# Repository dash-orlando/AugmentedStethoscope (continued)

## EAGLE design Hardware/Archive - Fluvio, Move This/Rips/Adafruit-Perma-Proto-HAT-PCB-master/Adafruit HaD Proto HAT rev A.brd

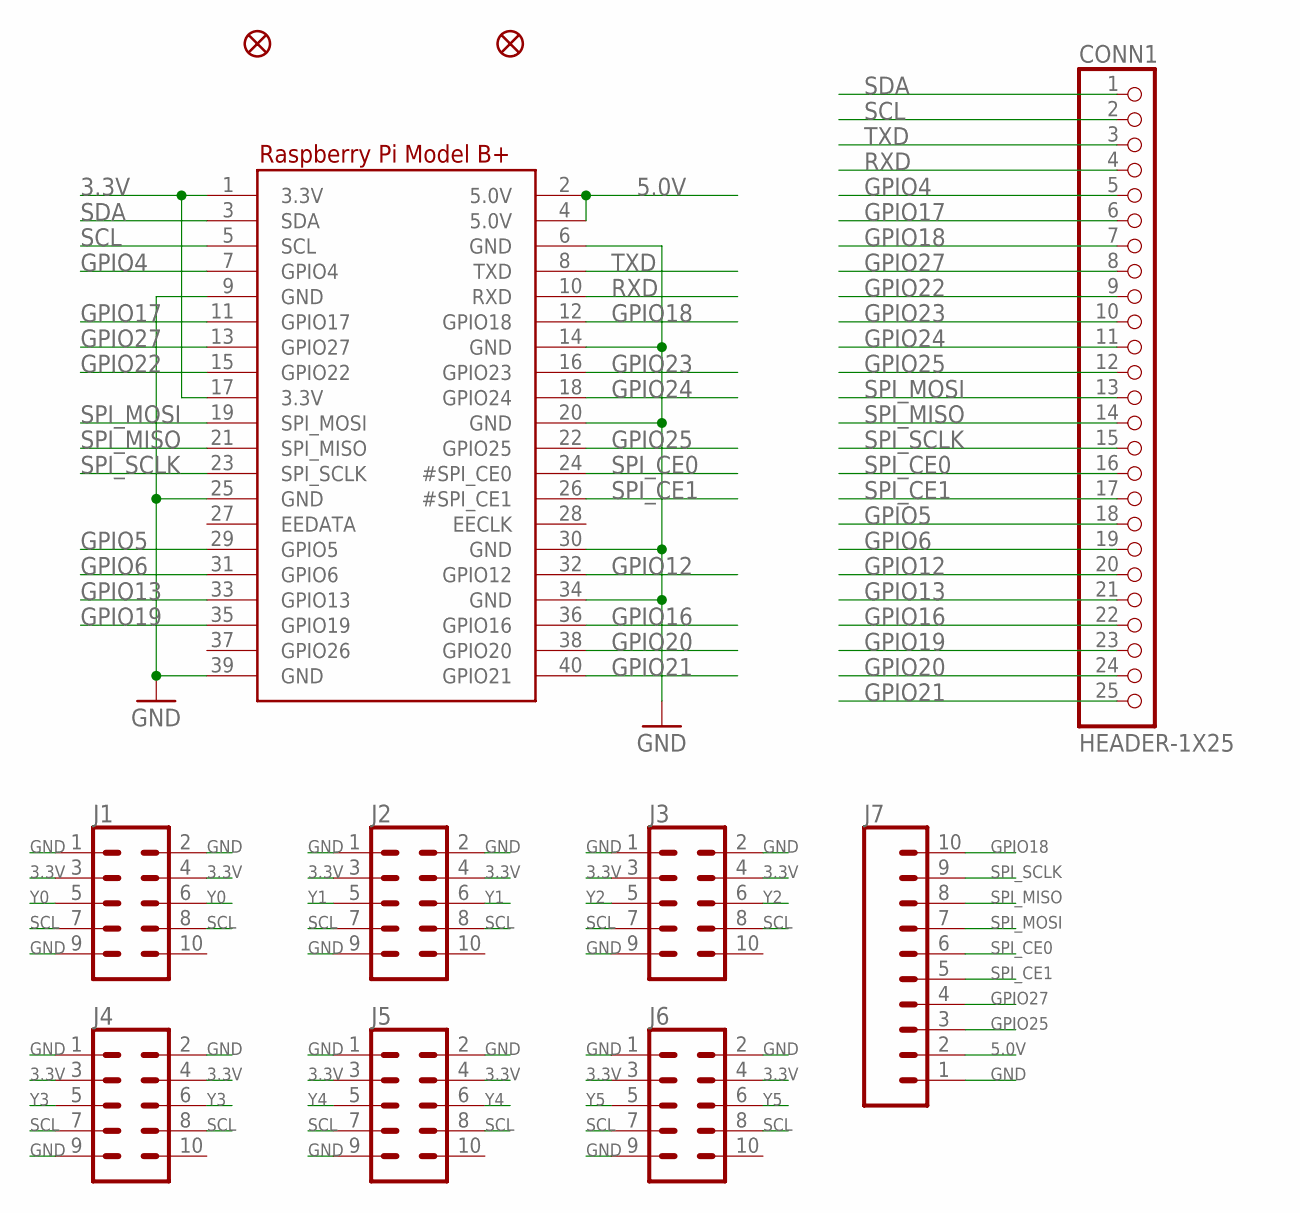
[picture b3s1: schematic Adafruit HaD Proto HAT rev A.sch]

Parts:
CONN1: HEADER-1X25; 1X25_ROUND_70MIL
FID2, FID3: FIDUCIAL""; FIDUCIAL_1MM
J1, J2, J3, J4, J5, J6: CONN_05X2SHD; 2X5-SHROUDED
J7: CONN_10LOCK; 1X10_LOCK
RPI1: RASPBERRYPI_BPLUS_HATNOSLOTS; PI_HAT_NOSLOTS

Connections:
3.3V: J1.3, J1.4, J2.3, J2.4, J3.3, J3.4, J4.3, J4.4, J5.3, J5.4, J6.3, J6.4, RPI1.1 (3.3V), RPI1.17 (3.3V)
5.0V: J7.2, RPI1.2 (5.0V), RPI1.4 (5.0V)
GND: J1.1, J1.2, J1.9, J2.1, J2.2, J2.9, J3.1, J3.2, J3.9, J4.1, J4.2, J4.9, J5.1, J5.2, J5.9, J6.1, J6.2, J6.9, J7.1, RPI1.6 (GND), RPI1.9 (GND), RPI1.14 (GND), RPI1.20 (GND), RPI1.25 (GND), RPI1.30 (GND), RPI1.34 (GND), RPI1.39 (GND)
GPIO4: CONN1.5, RPI1.7 (GPIO4)
GPIO5: CONN1.18, RPI1.29 (GPIO5)
GPIO6: CONN1.19, RPI1.31 (GPIO6)
GPIO12: CONN1.20, RPI1.32 (GPIO12)
GPIO13: CONN1.21, RPI1.33 (GPIO13)
GPIO16: CONN1.22, RPI1.36 (GPIO16)
GPIO17: CONN1.6, RPI1.11 (GPIO17)
GPIO18: CONN1.7, J7.10, RPI1.12 (GPIO18)
GPIO19: CONN1.23, RPI1.35 (GPIO19)
GPIO20: CONN1.24, RPI1.38 (GPIO20)
GPIO21: CONN1.25, RPI1.40 (GPIO21)
GPIO22: CONN1.9, RPI1.15 (GPIO22)
GPIO23: CONN1.10, RPI1.16 (GPIO23)
GPIO24: CONN1.11, RPI1.18 (GPIO24)
GPIO25: CONN1.12, J7.3, RPI1.22 (GPIO25)
GPIO27: CONN1.8, J7.4, RPI1.13 (GPIO27)
RXD: CONN1.4, RPI1.10 (RXD)
SCL: CONN1.2, J1.7, J1.8, J2.7, J2.8, J3.7, J3.8, J4.7, J4.8, J5.7, J5.8, J6.7, J6.8, RPI1.5 (SCL)
SDA: CONN1.1, RPI1.3 (SDA)
SPI_CE0: CONN1.16, J7.6, RPI1.24 (#SPI_CE0)
SPI_CE1: CONN1.17, J7.5, RPI1.26 (#SPI_CE1)
SPI_MISO: CONN1.14, J7.8, RPI1.21 (SPI_MISO)
SPI_MOSI: CONN1.13, J7.7, RPI1.19 (SPI_MOSI)
SPI_SCLK: CONN1.15, J7.9, RPI1.23 (SPI_SCLK)
TXD: CONN1.3, RPI1.8 (TXD)
Y0: J1.5, J1.6
Y1: J2.5, J2.6
Y2: J3.5, J3.6
Y3: J4.5, J4.6
Y4: J5.5, J5.6
Y5: J6.5, J6.6

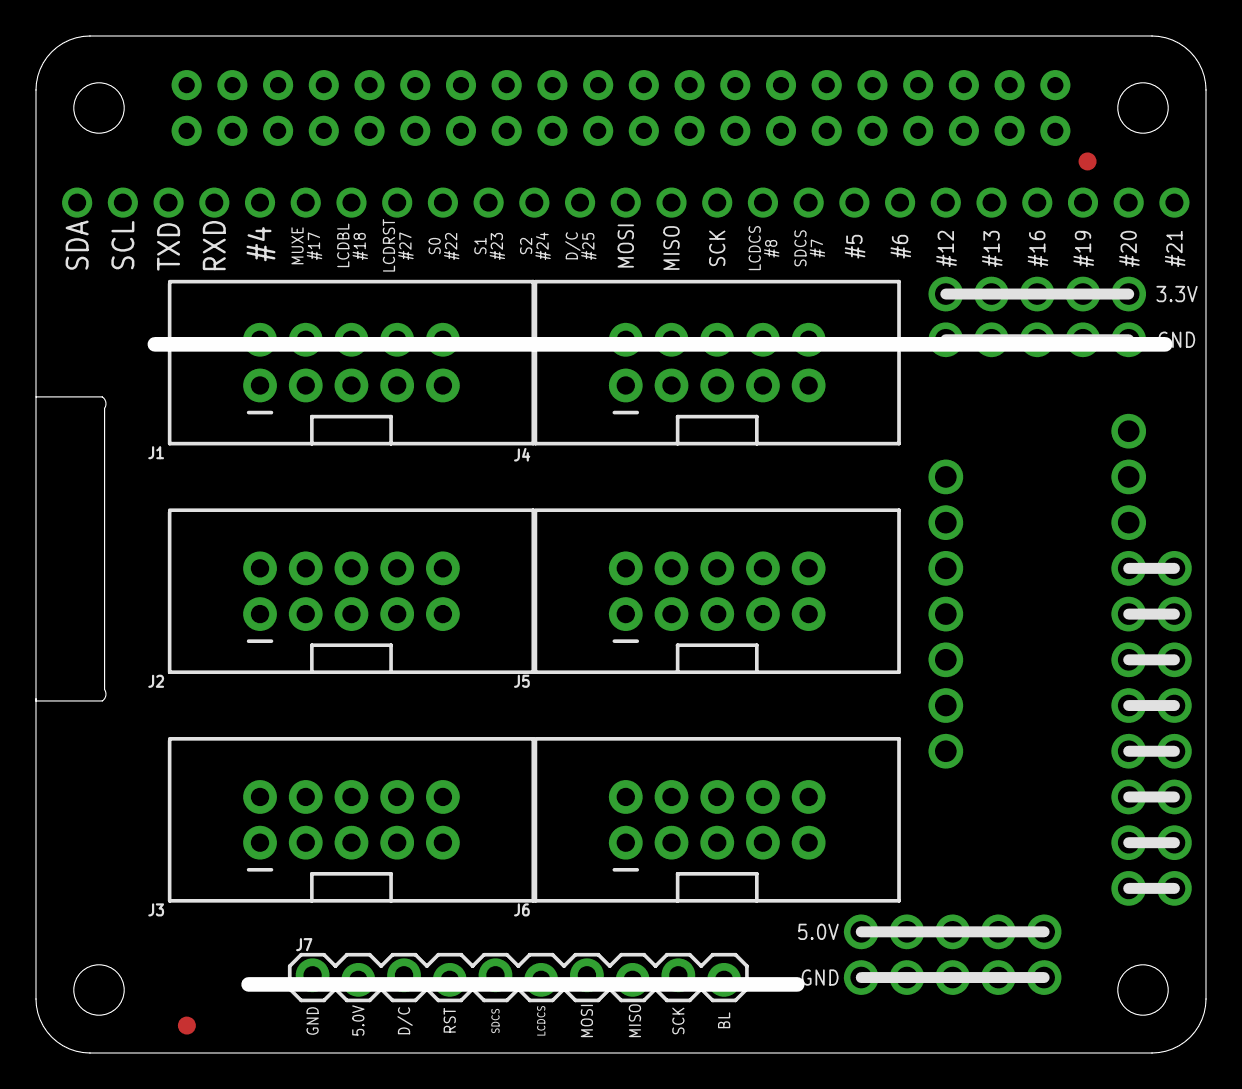
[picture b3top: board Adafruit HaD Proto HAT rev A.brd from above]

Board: 2 copper layers, 65.0 x 56.5 mm, 11 parts (0 on the bottom side), 34 nets.

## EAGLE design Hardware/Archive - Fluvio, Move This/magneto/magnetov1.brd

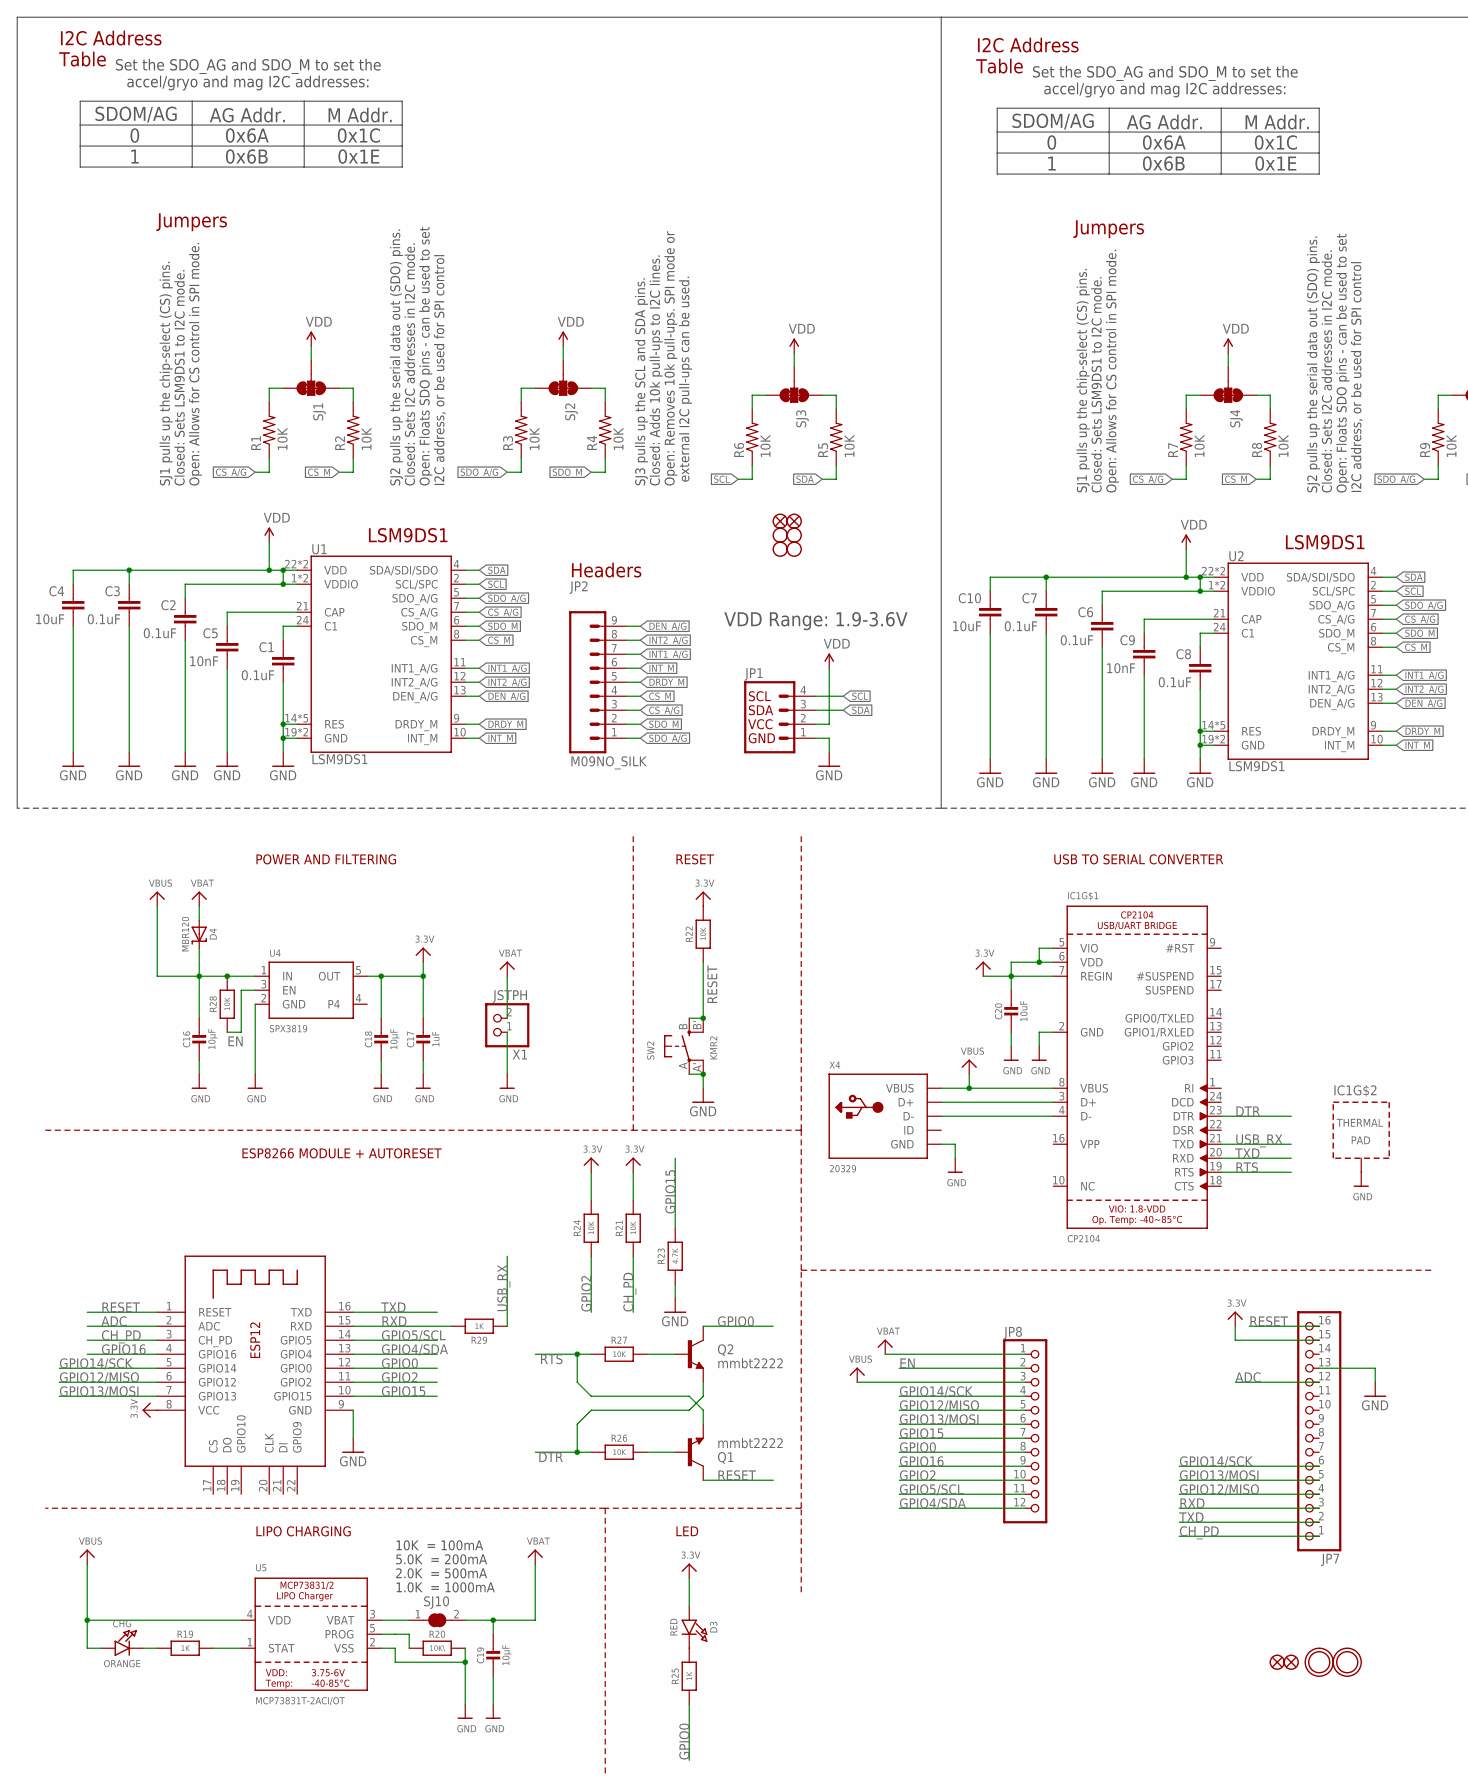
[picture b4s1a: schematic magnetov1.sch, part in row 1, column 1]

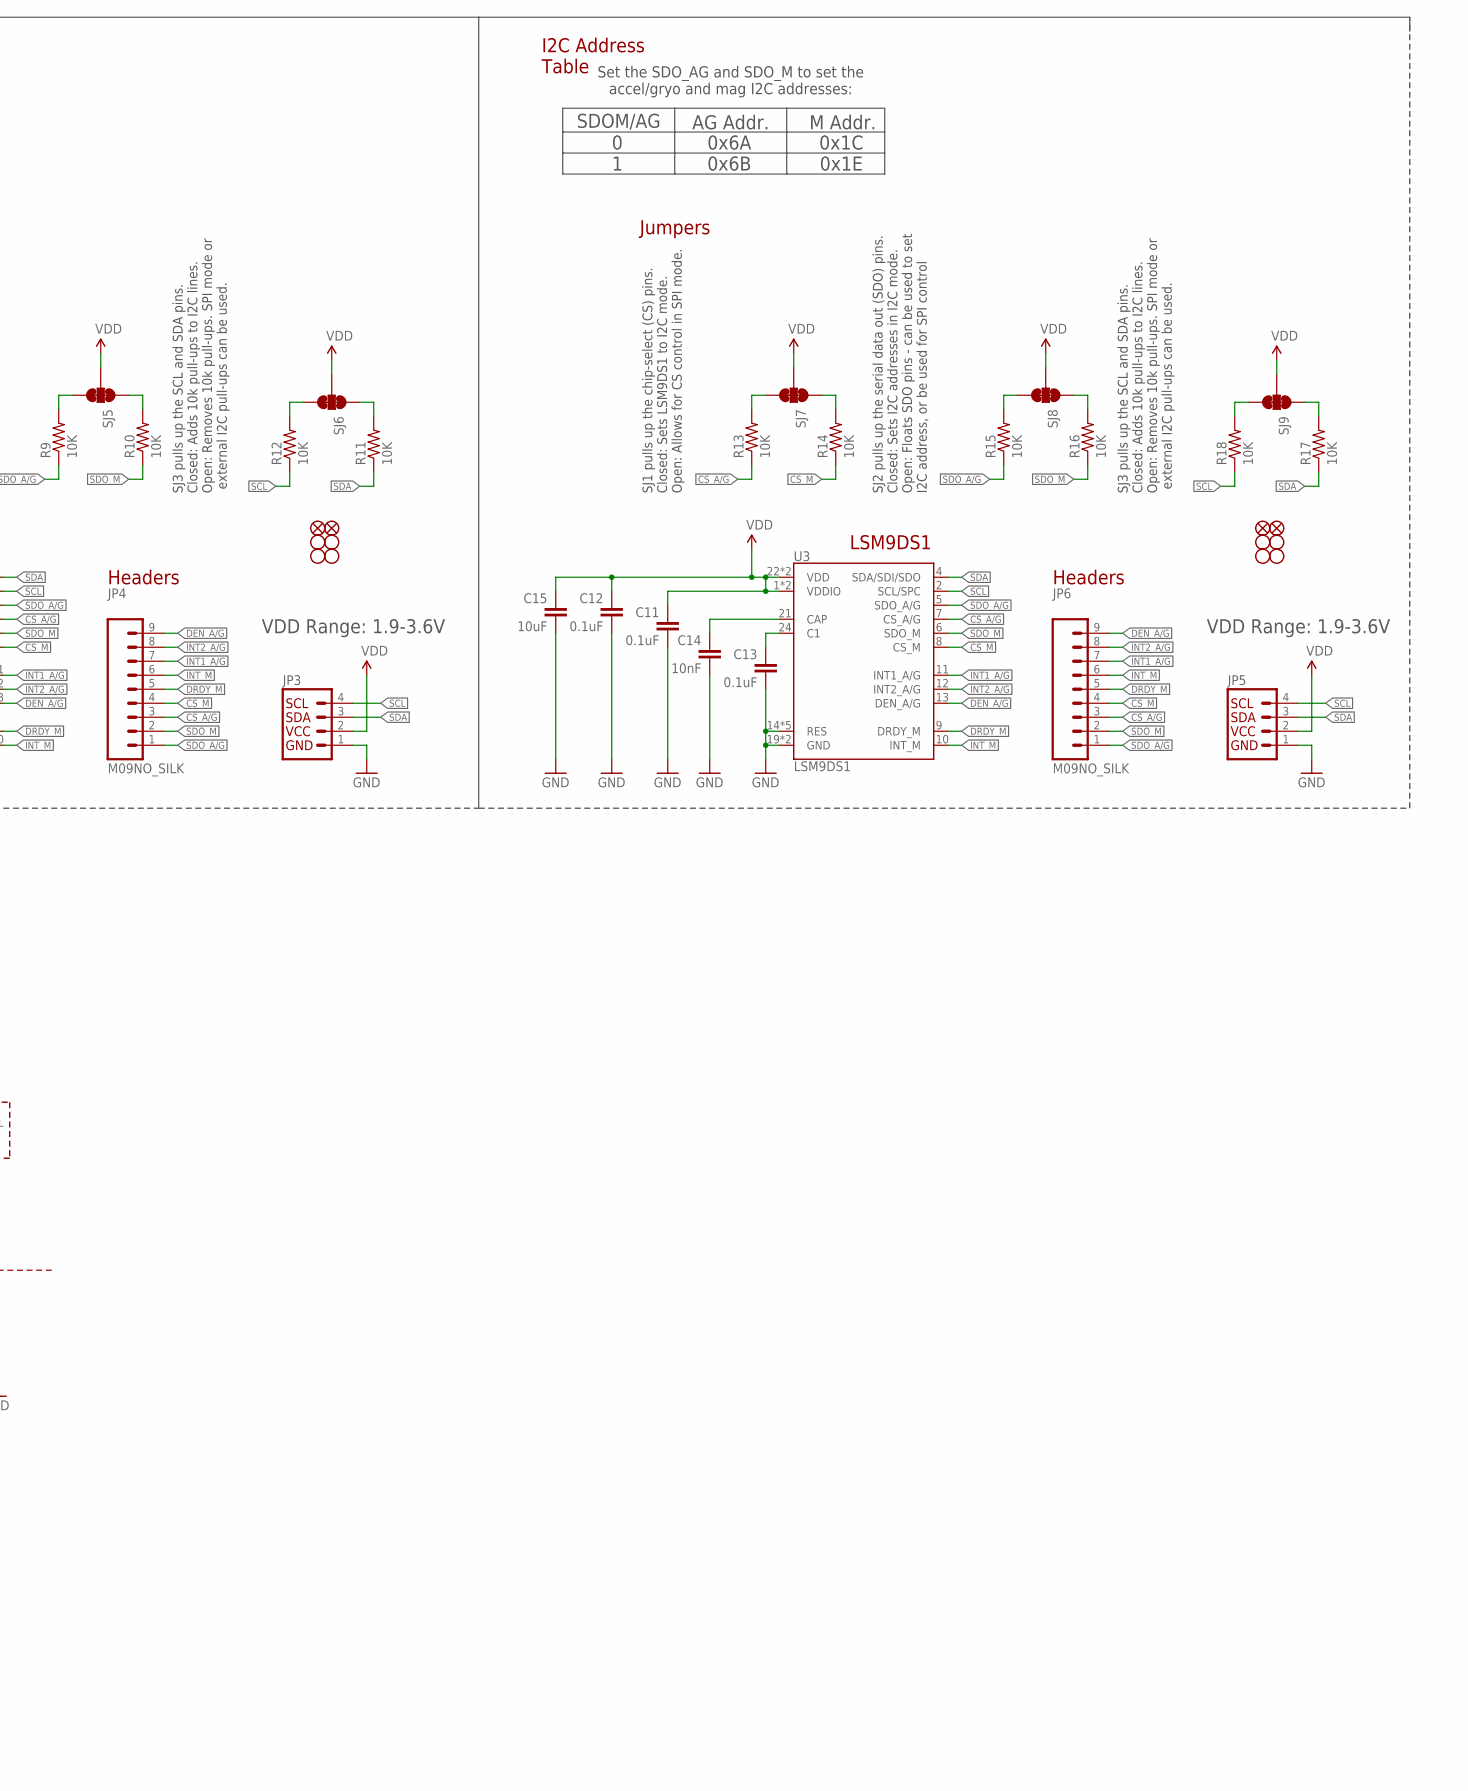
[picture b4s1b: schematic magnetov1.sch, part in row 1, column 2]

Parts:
C1, C2, C3, C6, C7, C8, C11, C12, C13: 0.1uF; 0603-CAP
C4, C10, C15: 10uF; 0603-CAP
C5, C9, C14: 10nF; 0603-CAP
C16, C18, C19: 10µF; 0805-NO
C17: 1uF; 0603-NO
C20: 10uF; 0805-NO
CHG: ORANGE; CHIPLED_0805_NOOUTLINE
D3: RED; CHIPLED_0805_NOOUTLINE
D4: MBR120; SOD-123
FID1, FID2, FID3, FID4, FID5, FID6: FIDUCIAL1X2; FIDUCIAL-1X2
IC1: CP2104; QFN24_4MM_SMSC
JP1, JP3, JP5: I2C_STANDARD_NO_SILK; 1X04_NO_SILK
JP2, JP4, JP6: M09NO_SILK; 1X09_NO_SILK
JP7: HEADER-1X16ROUND; 1X16_ROUND
JP8: HEADER-1X12; 1X12_ROUND
Q1, Q2: mmbt2222; SOT23-3
R1, R2, R3, R4, R5, R6, R7, R8, R9, R10, R11, R12, R13, R14, R15, R16, R17, R18: 10K; 0603-RES
R19, R25: 1K; 0603-NO
R20: 10K\; 0603-NO
R21, R22, R24, R26, R28: 10K; 0603-NO
R23: 4.7K; 0603-NO
R27: 10K; _0603MP
R29: 1K; _0603MP
SJ1, SJ2, SJ3, SJ4, SJ5, SJ6, SJ7, SJ8, SJ9: JUMPER-PAD-3-NC_BY_TRACE; PAD-JUMPER-3-3OF3_NC_BY_TRACE_YES_SILK_FULL_BOX
SJ10: SOLDERJUMPER_CLOSED; SOLDERJUMPER_CLOSEDWIRE
STANDOFF1, STANDOFF2, STANDOFF3, STANDOFF4, STANDOFF5, STANDOFF6, STANDOFF7, STANDOFF8, STANDOFF9, STANDOFF10, STANDOFF11, STANDOFF12: STAND-OFF
SW2: KMR2; BTN_KMR2_4.6X2.8
U1, U2, U3: LSM9DS1; LGA24-8X4
U4: SPX3819; SOT23-5
U5: MCP73831T-2ACI/OT; SOT23-5
U$31, U$32: MOUNTINGHOLE2.5; MOUNTINGHOLE_2.5_PLATED
U$34, U$35: FIDUCIAL""; FIDUCIAL_1MM
X1: JSTPH; JSTPH2
X2: ESP-12; ESP-12E
X4: 20329; 4UCONN_20329_V2

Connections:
3.3V: C17.1, C18.1, C20.1, D3.A, IC1.5 (VIO), IC1.6 (VDD), IC1.7 (REGIN), JP7.15, R21.2, R22.2, R24.2, U4.5 (OUT), X2.8 (VCC)
ADC: JP7.12, X2.2 (ADC)
C1: C1.1, U1.24 (C1)
C2: C8.1, U2.24 (C1)
C3: C13.1, U3.24 (C1)
CAP: C5.1, U1.21 (CAP)
CAP1: C9.1, U2.21 (CAP)
CAP2: C14.1, U3.21 (CAP)
CH_PD: JP7.1, R21.1, X2.3 (CH_PD)
CS_A/G: JP2.3, JP4.3, JP6.3, R1.1, R7.1, R13.1, U1.7 (CS_A/G), U2.7 (CS_A/G), U3.7 (CS_A/G)
CS_A/G_PU: R1.2, SJ1.3
CS_A/G_PU1: R7.2, SJ4.3
CS_A/G_PU2: R13.2, SJ7.3
CS_M: JP2.4, JP4.4, JP6.4, R2.1, R8.1, R14.1, U1.8 (CS_M), U2.8 (CS_M), U3.8 (CS_M)
CS_M_PU: R2.2, SJ1.1
CS_M_PU1: R8.2, SJ4.1
CS_M_PU2: R14.2, SJ7.1
DEN_A/G: JP2.9, JP4.9, JP6.9, U1.13 (DEN_A/G), U2.13 (DEN_A/G), U3.13 (DEN_A/G)
DRDY_M: JP2.5, JP4.5, JP6.5, U1.9 (DRDY_M), U2.9 (DRDY_M), U3.9 (DRDY_M)
DTR: IC1.23 (DTR), Q2.2 (E), R26.1
EN: JP8.2, R28.1, U4.3 (EN)
GND: C1.2, C2.2, C3.2, C4.2, C5.2, C6.2, C7.2, C8.2, C9.2, C10.2, C11.2, C12.2, C13.2, C14.2, C15.2, C16.2, C17.2, C18.2, C19.2, C20.2, IC1.2 (GND), IC1.THERM (TP), JP1.1, JP3.1, JP5.1, JP7.13, R20.2, R23.1, SW2.A, SW2.A' (P1), U1.14 (RES), U1.15 (RES), U1.16 (RES), U1.17 (RES), U1.18 (RES), U1.19 (GND), U1.20 (GND), U2.14 (RES), U2.15 (RES), U2.16 (RES), U2.17 (RES), U2.18 (RES), U2.19 (GND), U2.20 (GND), U3.14 (RES), U3.15 (RES), U3.16 (RES), U3.17 (RES), U3.18 (RES), U3.19 (GND), U3.20 (GND), U4.2 (GND), U5.2 (VSS), X1.1, X2.9 (GND), X4.BASE@1 (GND), X4.BASE@2 (GND), X4.GND, X4.SPRT@1 (GND), X4.SPRT@2 (GND), X4.SPRT@3 (GND), X4.SPRT@4 (GND)
GPIO0: JP8.8, Q2.3 (C), R25.1, X2.12 (GPIO0)
GPIO2: JP8.10, R24.1, X2.11 (GPIO2)
GPIO4/SDA: JP8.12, X2.13 (GPIO4)
GPIO5/SCL: JP8.11, X2.14 (GPIO5)
GPIO12/MISO: JP7.4, JP8.5, X2.6 (GPIO12)
GPIO13/MOSI: JP7.5, JP8.6, X2.7 (GPIO13)
GPIO14/SCK: JP7.6, JP8.4, X2.5 (GPIO14)
GPIO15: JP8.7, R23.2, X2.10 (GPIO15)
GPIO16: JP8.9, X2.4 (GPIO16)
INT1_A/G: JP2.7, JP4.7, JP6.7, U1.11 (INT1_A/G), U2.11 (INT1_A/G), U3.11 (INT1_A/G)
INT2_A/G: JP2.8, JP4.8, JP6.8, U1.12 (INT2_A/G), U2.12 (INT2_A/G), U3.12 (INT2_A/G)
INT_M: JP2.6, JP4.6, JP6.6, U1.10 (INT_M), U2.10 (INT_M), U3.10 (INT_M)
unnamed: CHG.C, R19.1
unnamed: IC1.3 (D+), X4.D+
unnamed: R19.2, U5.1 (STAT)
unnamed: R20.1, U5.5 (PROG)
unnamed: D3.C, R25.2
unnamed: IC1.4 (D-), X4.D-
unnamed: SJ10.1, U5.3 (VBAT)
unnamed: Q1.1 (B), R26.2
unnamed: Q2.1 (B), R27.2
RESET: JP7.16, Q1.3 (C), R22.1, SW2.B (S), SW2.B' (S1), X2.1 (RESET)
RTS: IC1.19 (RTS), Q1.2 (E), R27.1
RXD: JP7.3, R29.2, X2.15 (RXD)
SCL: JP1.4, JP3.4, JP5.4, R6.1, R12.1, R18.1, U1.2 (SCL/SPC), U2.2 (SCL/SPC), U3.2 (SCL/SPC)
SCL_PU: R6.2, SJ3.3
SCL_PU1: R12.2, SJ6.3
SCL_PU2: R18.2, SJ9.3
SDA: JP1.3, JP3.3, JP5.3, R5.1, R11.1, R17.1, U1.4 (SDA/SDI/SDO), U2.4 (SDA/SDI/SDO), U3.4 (SDA/SDI/SDO)
SDA_PU: R5.2, SJ3.1
SDA_PU1: R11.2, SJ6.1
SDA_PU2: R17.2, SJ9.1
SDO_A/G: JP2.1, JP4.1, JP6.1, R3.1, R9.1, R15.1, U1.5 (SDO_A/G), U2.5 (SDO_A/G), U3.5 (SDO_A/G)
SDO_A/G_PU: R3.2, SJ2.3
SDO_A/G_PU1: R9.2, SJ5.3
SDO_A/G_PU2: R15.2, SJ8.3
SDO_M: JP2.2, JP4.2, JP6.2, R4.1, R10.1, R16.1, U1.6 (SDO_M), U2.6 (SDO_M), U3.6 (SDO_M)
SDO_M_PU: R4.2, SJ2.1
SDO_M_PU1: R10.2, SJ5.1
SDO_M_PU2: R16.2, SJ8.1
TXD: IC1.20 (RXD), JP7.2, X2.16 (TXD)
USB_RX: IC1.21 (TXD), R29.1
VBAT: C19.1, D4.A, JP8.1, SJ10.2, X1.2
VBUS: C16.1, CHG.A, D4.C, IC1.8 (VBUS), JP8.3, R28.2, U4.1 (IN), U5.4 (VDD), X4.VBUS
VDD: C2.1, C3.1, C4.1, C6.1, C7.1, C10.1, C11.1, C12.1, C15.1, JP1.2, JP3.2, JP5.2, SJ1.2, SJ2.2, SJ3.2, SJ4.2, SJ5.2, SJ6.2, SJ7.2, SJ8.2, SJ9.2, U1.1 (VDDIO), U1.3 (VDDIO), U1.22 (VDD), U1.23 (VDD), U2.1 (VDDIO), U2.3 (VDDIO), U2.22 (VDD), U2.23 (VDD), U3.1 (VDDIO), U3.3 (VDDIO), U3.22 (VDD), U3.23 (VDD)

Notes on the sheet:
SDOM/AG
0x1C 0x1E
AG Addr.
0 1
M Addr.
0x6A 0x6B
Set the SDO_AG and SDO_M to set the accel/gryo and mag I2C addresses:
SJ1 pulls up the chip-select (CS) pins. Closed: Sets LSM9DS1 to I2C mode. Open: Allows for CS control in SPI mode.
SJ2 pulls up the serial data out (SDO) pins. Closed: Sets I2C addresses in I2C mode. Open: Floats SDO pins - can be used to set I2C address, or be used for SPI control
SJ3 pulls up the SCL and SDA pins. Closed: Adds 10k pull-ups to I2C lines. Open: Removes 10k pull-ups. SPI mode or external I2C pull-ups can be used.
Jumpers
I2C Address Table
LSM9DS1
Headers
VDD Range: 1.9-3.6V
POWER AND FILTERING
RESET
10K = 100mA
5.0K = 200mA
2.0K = 500mA
1.0K = 1000mA
USB TO SERIAL CONVERTER
LIPO CHARGING
LED
ESP8266 MODULE + AUTORESET

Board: 2 copper layers, 104 parts (0 on the bottom side), 67 nets, no tracks yet.

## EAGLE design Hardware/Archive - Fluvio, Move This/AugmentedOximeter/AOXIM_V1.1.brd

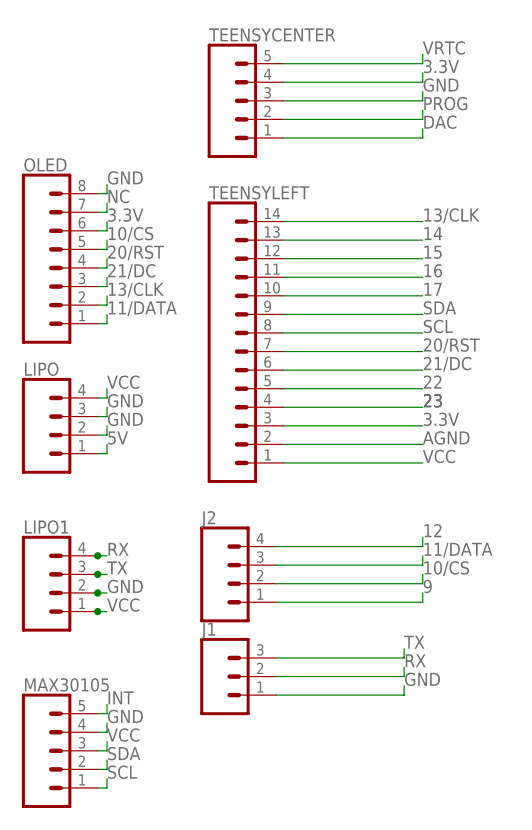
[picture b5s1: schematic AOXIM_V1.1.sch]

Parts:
J1: CONN_03; 1X03
J2: CONN_04; 1X04
LIPO, LIPO1: CONN_04; 1X04
MAX30105: CONN_05; 1X05
OLED: CONN_08"; 1X08
TEENSYCENTER: CONN_05; 1X05
TEENSYLEFT: CONN_14; 1X14

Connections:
3.3V: OLED.6, TEENSYCENTER.4, TEENSYLEFT.3
5V: LIPO.1
9: J2.1
10/CS: J2.2, OLED.5
11/DATA: J2.3, OLED.1
12: J2.4
13/CLK: OLED.2, TEENSYLEFT.14
14: TEENSYLEFT.13
15: TEENSYLEFT.12
16: TEENSYLEFT.11
17: TEENSYLEFT.10
20/RST: OLED.4, TEENSYLEFT.7
21/DC: OLED.3, TEENSYLEFT.6
22: TEENSYLEFT.5
23: TEENSYLEFT.4
AGND: TEENSYLEFT.2
DAC: TEENSYCENTER.1
GND: J1.1, LIPO.2, LIPO.3, LIPO1.2, MAX30105.4, OLED.8, TEENSYCENTER.3
INT: MAX30105.5
NC: OLED.7
PROG: TEENSYCENTER.2
RX: J1.2, LIPO1.4
SCL: MAX30105.1, TEENSYLEFT.8
SDA: MAX30105.2, TEENSYLEFT.9
TX: J1.3, LIPO1.3
VCC: LIPO.4, LIPO1.1, MAX30105.3, TEENSYLEFT.1
VRTC: TEENSYCENTER.5

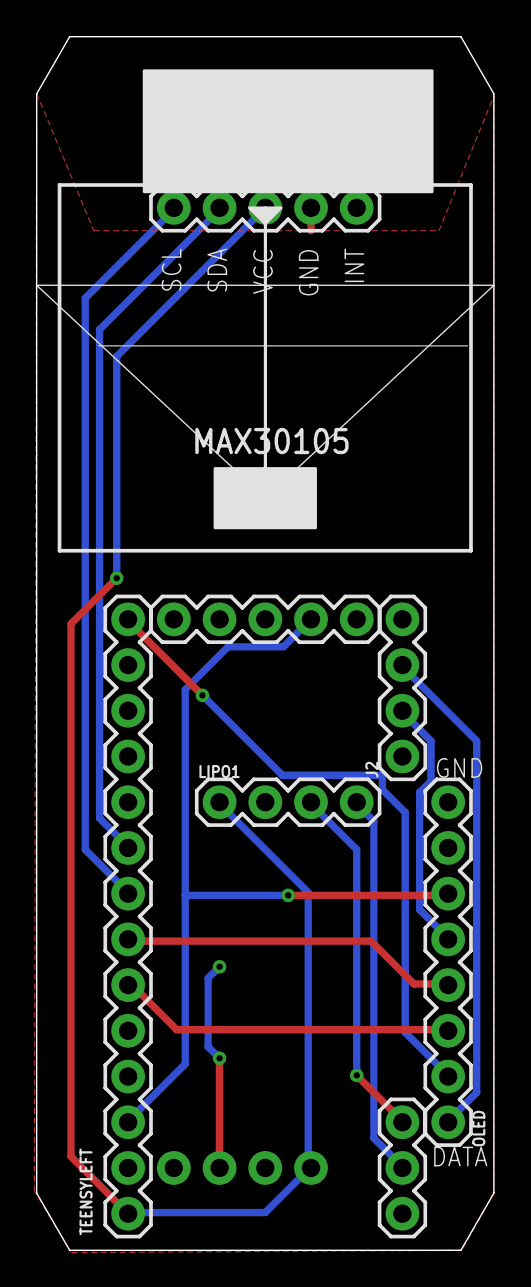
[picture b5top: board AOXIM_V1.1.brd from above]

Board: 2 copper layers, 25.4 x 67.4 mm, 8 parts (1 on the bottom side), 12 nets.

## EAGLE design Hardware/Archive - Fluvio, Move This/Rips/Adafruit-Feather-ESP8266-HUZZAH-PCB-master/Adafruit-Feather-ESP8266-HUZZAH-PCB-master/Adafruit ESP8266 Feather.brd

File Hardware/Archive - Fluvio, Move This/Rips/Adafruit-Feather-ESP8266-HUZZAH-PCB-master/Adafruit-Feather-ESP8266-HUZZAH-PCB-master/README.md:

# Adafruit-Feather-ESP8266-HUZZAH-PCB
PCB files for the Adafruit Feather ESP8266 HUZZAH

Format is EagleCAD schematic and board layout

For more details, check out the product page at

  * https://www.adafruit.com/product/2821

Adafruit invests time and resources providing this open source design, 
please support Adafruit and open-source hardware by purchasing 
products from Adafruit!

Designed by Adafruit Industries.  
Creative Commons Attribution, Share-Alike license, check license.txt for more information
All text above must be included in any redistribution

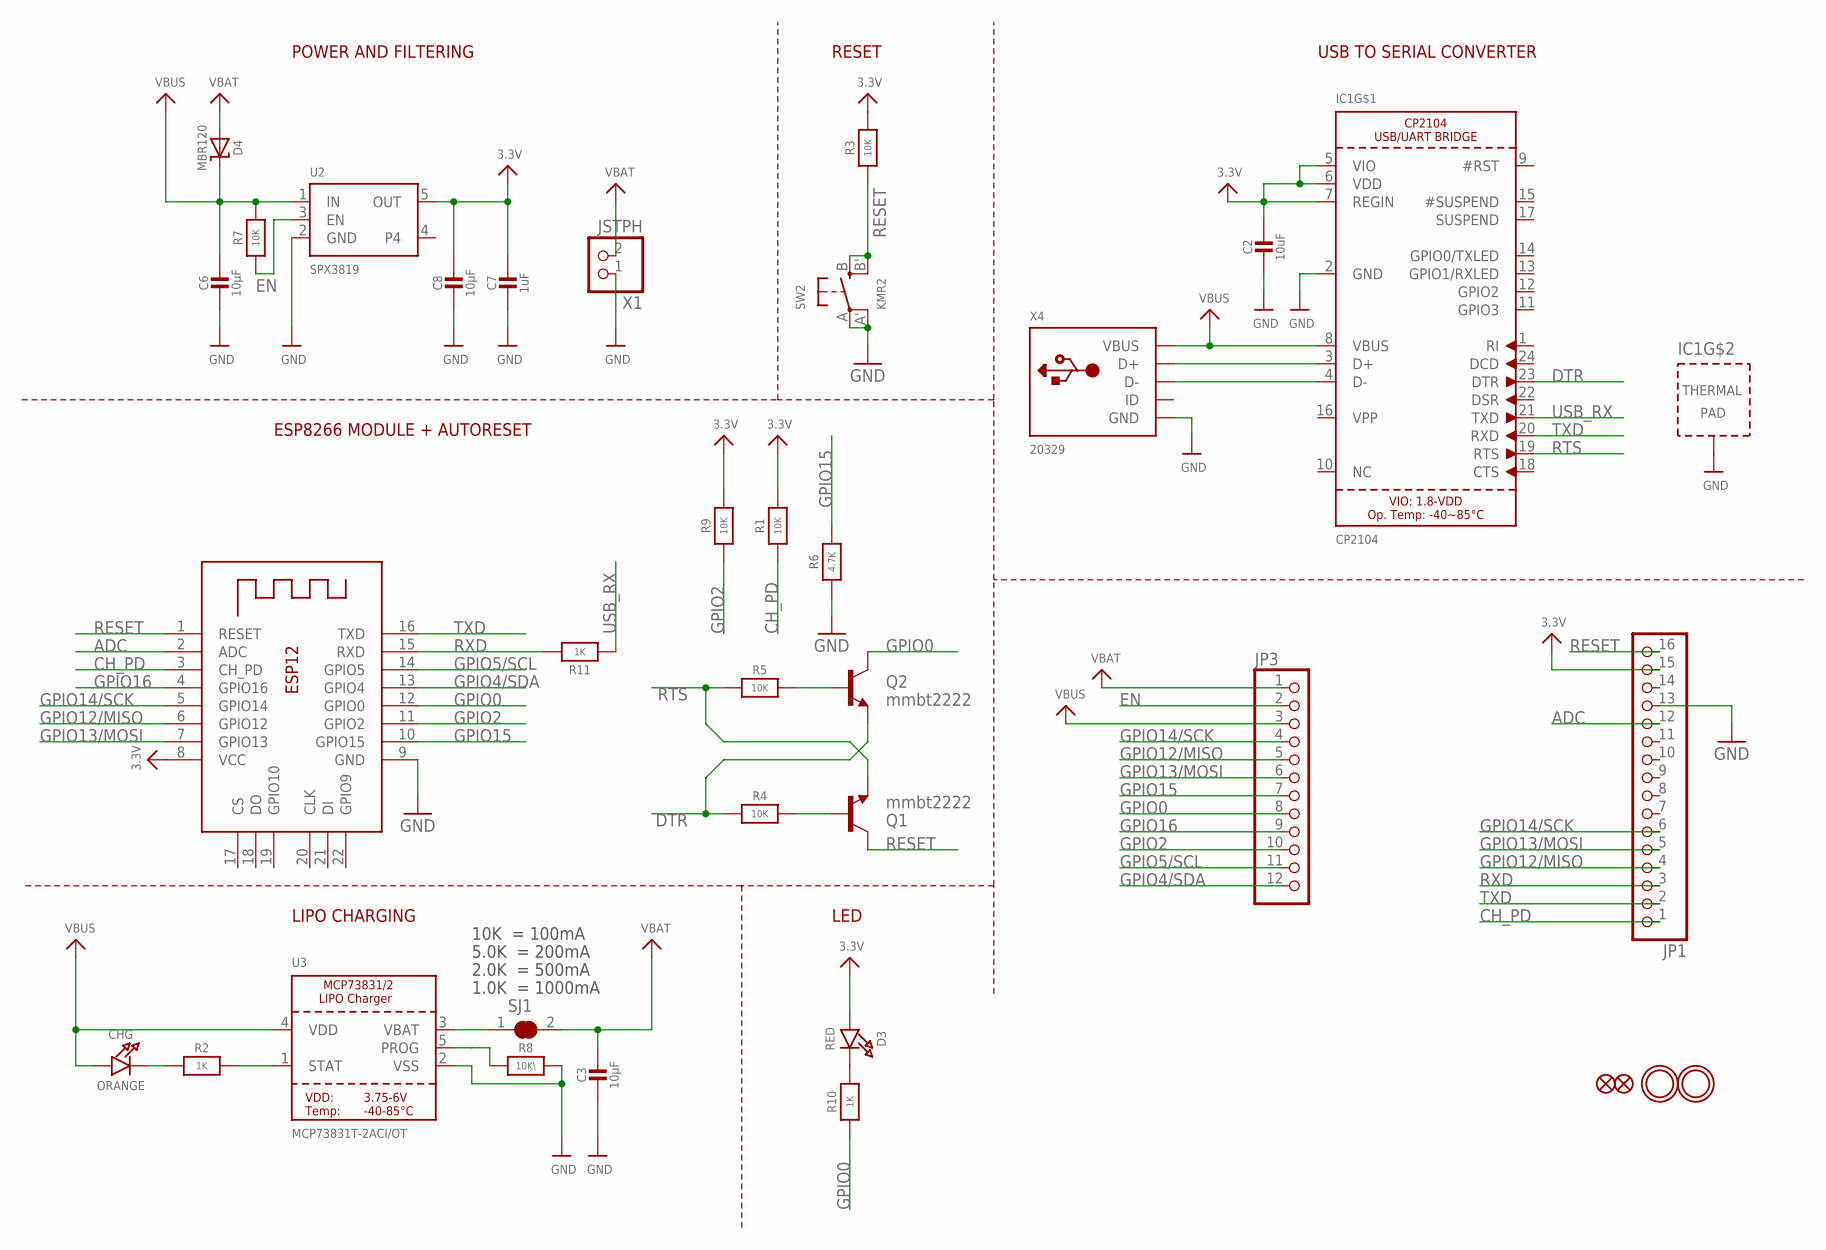
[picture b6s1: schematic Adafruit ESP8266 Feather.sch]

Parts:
C2: 10uF; 0805-NO
C3, C6, C8: 10µF; 0805-NO
C7: 1uF; 0603-NO
CHG: ORANGE; CHIPLED_0805_NOOUTLINE
D3: RED; CHIPLED_0805_NOOUTLINE
D4: MBR120; SOD-123
IC1: CP2104; QFN24_4MM_SMSC
JP1: HEADER-1X16ROUND; 1X16_ROUND
JP3: HEADER-1X12; 1X12_ROUND
Q1, Q2: mmbt2222; SOT23-3
R1, R3, R4, R7, R9: 10K; 0603-NO
R2, R10: 1K; 0603-NO
R5: 10K; _0603MP
R6: 4.7K; 0603-NO
R8: 10K\; 0603-NO
R11: 1K; _0603MP
SJ1: SOLDERJUMPER_CLOSED; SOLDERJUMPER_CLOSEDWIRE
SW2: KMR2; BTN_KMR2_4.6X2.8
U2: SPX3819; SOT23-5
U3: MCP73831T-2ACI/OT; SOT23-5
U$31, U$32: MOUNTINGHOLE2.5; MOUNTINGHOLE_2.5_PLATED
U$34, U$35: FIDUCIAL""; FIDUCIAL_1MM
X1: JSTPH; JSTPH2
X2: ESP-12; ESP-12E
X4: 20329; 4UCONN_20329_V2

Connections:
3.3V: C2.1, C7.1, C8.1, D3.A, IC1.5 (VIO), IC1.6 (VDD), IC1.7 (REGIN), JP1.15, R1.2, R3.2, R9.2, U2.5 (OUT), X2.8 (VCC)
ADC: JP1.12, X2.2 (ADC)
CH_PD: JP1.1, R1.1, X2.3 (CH_PD)
DTR: IC1.23 (DTR), Q2.2 (E), R4.1
EN: JP3.2, R7.1, U2.3 (EN)
GND: C2.2, C3.2, C6.2, C7.2, C8.2, IC1.2 (GND), IC1.THERM (TP), JP1.13, R6.1, R8.2, SW2.A, SW2.A' (P1), U2.2 (GND), U3.2 (VSS), X1.1, X2.9 (GND), X4.BASE@1 (GND), X4.BASE@2 (GND), X4.GND, X4.SPRT@1 (GND), X4.SPRT@2 (GND), X4.SPRT@3 (GND), X4.SPRT@4 (GND)
GPIO0: JP3.8, Q2.3 (C), R10.1, X2.12 (GPIO0)
GPIO2: JP3.10, R9.1, X2.11 (GPIO2)
GPIO4/SDA: JP3.12, X2.13 (GPIO4)
GPIO5/SCL: JP3.11, X2.14 (GPIO5)
GPIO12/MISO: JP1.4, JP3.5, X2.6 (GPIO12)
GPIO13/MOSI: JP1.5, JP3.6, X2.7 (GPIO13)
GPIO14/SCK: JP1.6, JP3.4, X2.5 (GPIO14)
GPIO15: JP3.7, R6.2, X2.10 (GPIO15)
GPIO16: JP3.9, X2.4 (GPIO16)
unnamed: CHG.C, R2.1
unnamed: IC1.3 (D+), X4.D+
unnamed: R2.2, U3.1 (STAT)
unnamed: R8.1, U3.5 (PROG)
unnamed: D3.C, R10.2
unnamed: IC1.4 (D-), X4.D-
unnamed: SJ1.1, U3.3 (VBAT)
unnamed: Q1.1 (B), R4.2
unnamed: Q2.1 (B), R5.2
RESET: JP1.16, Q1.3 (C), R3.1, SW2.B (S), SW2.B' (S1), X2.1 (RESET)
RTS: IC1.19 (RTS), Q1.2 (E), R5.1
RXD: JP1.3, R11.2, X2.15 (RXD)
TXD: IC1.20 (RXD), JP1.2, X2.16 (TXD)
USB_RX: IC1.21 (TXD), R11.1
VBAT: C3.1, D4.A, JP3.1, SJ1.2, X1.2
VBUS: C6.1, CHG.A, D4.C, IC1.8 (VBUS), JP3.3, R7.2, U2.1 (IN), U3.4 (VDD), X4.VBUS

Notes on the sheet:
POWER AND FILTERING
RESET
10K = 100mA
5.0K = 200mA
2.0K = 500mA
1.0K = 1000mA
USB TO SERIAL CONVERTER
LIPO CHARGING
LED
ESP8266 MODULE + AUTORESET

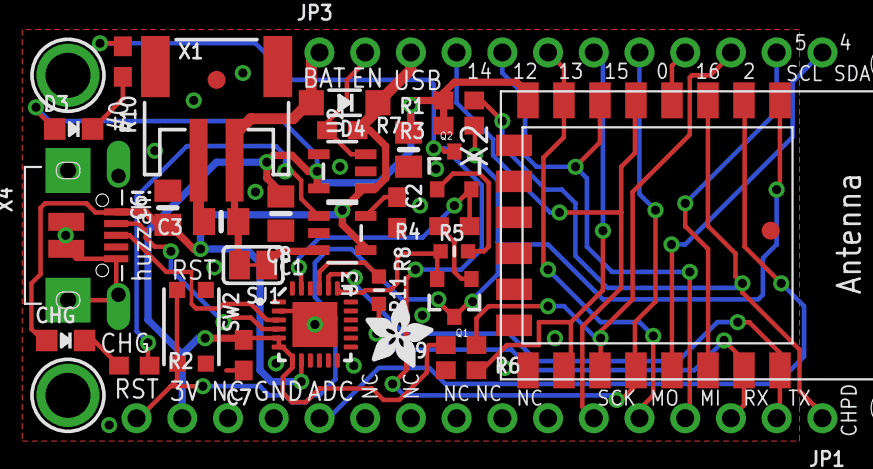
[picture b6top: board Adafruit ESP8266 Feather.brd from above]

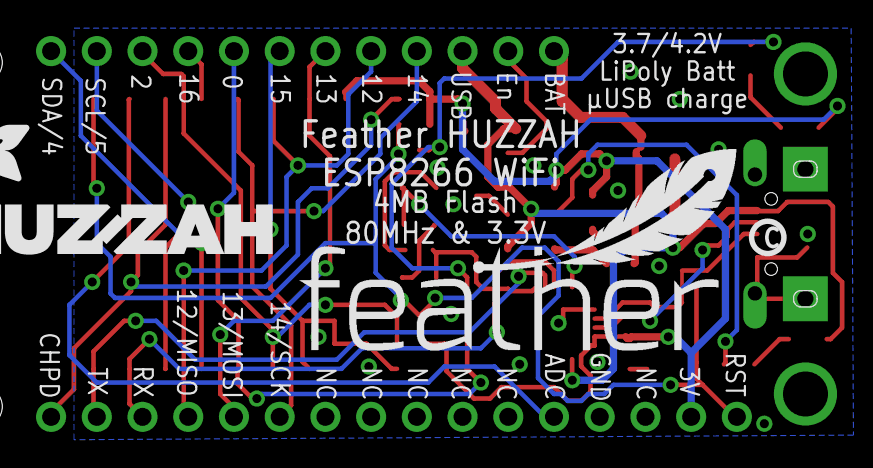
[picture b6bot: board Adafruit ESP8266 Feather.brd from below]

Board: 2 copper layers, 40 parts (4 on the bottom side), 31 nets.

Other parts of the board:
U$7: ADAFRUIT_5MM
U$9: FEATHERLOGO
U$13: PCBFEAT-REV-040
U$15: ADAFRUIT_3.5MM
U$23: HUZZAHLOGO

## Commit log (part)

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2016-10-20 Updated the protocols with the newest variable definitions
2016-10-26 Adapted new modifications by MX.
2016-11-02 Changed the byte value for the variable definition shown in the protocol header file
2016-11-04 Added the configuration file protocol. This protocol will be used to pass data structures into the device functions.
2016-11-09 Fixed an issue with the variable structure created in the configuration file and used to pass file names into other functions
2016-11-10 Made some modification to the microphone parameters
2016-11-11 Created a new directory, under documentation, for the allocation of the disclosure and patent write-ups.
2016-11-14 Created a function called continue tracking. This function will be part of a set of function that uses the audio stream for analysis but does not record the data itself.
2016-11-15 Finished the tracking stream function but need to optimize serial monitor commands to improve the function.
2016-11-16 Added a stop tracking microphone stream function and its associated definitions. Tested the function successfully using the mobile-windows app.
2016-11-22 Integration of SerialFrame functions into the main body of code.
2016-11-28 Modified the output of the serial frame library to be a string instead of a byte.
2017-01-31 Created a new dev branch that reverts the stethoscope code to a single byte communication method.
2017-02-01 Successfully added the frame function that prints the heart rate to the tracking and the recording functions of the stethoscope.
2017-02-01 Added the blending feature to the parse byte function.
2017-03-07 Added a library of sound recordings made in our lab using the latest version of the stethoscope.
2017-04-03 First (untested) integration of BP augmentation
2017-04-23 Made functions to demo new blending and record2playback capabilities.
2017-06-16 Optimzed heartbeat detection algorithm--constraining S1-S2 interval to a definable range. Refactored many Audio-library object names from generic to descriptive ones.
2017-06-21 Found and added the missing sections of the recording function that triggered the writing of the data to the SD file.
2017-06-21 Added recordings for 2 more volunteers.
2017-06-22 Added some recordings from today.
2017-06-29 Created algorithms for the spectral analysis of input signals.
2017-07-06 Added comment on the process of installing binaries to a PC.
2017-07-07 Added references to the python files.
2017-07-07 Completed a signal gain modifying routine.
2017-07-07 Discovered and fixed the problem with the playback of recordings or other audio files. The filenames need to be 6 characters long.
2017-07-07 Re-factored the set of functions "tracking mic stream" to "heart beat monitoring" to be more specific and understandable.
2017-07-07 Reduced the number of SD files to be used.
2017-07-11 converted some wave files into .h/.cpp files using the wave2sketch application.
2017-07-11 Completed about 80% of the guide. Missing a description of the connections diagram.
2017-07-18 Reduced the mixer level on the blended SD file sound to reduce the effect of volume differences between recordings and the microphone line. This will become a more dynamic method in the future.
2017-07-18 Added a recorded korotkoff sound and implemented it by modifying the heart rate based on the length of the recording. Need to work on blending the play and end bytes.
2017-07-19 This code has been assembled to test the concept of contract free location sensing using magnetometers. Magnetic field vector data for two sensors is pulled from the serial port of an Arduino board. 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
2017-07-19 Adapted the example function for rms amplitude peaks to the audio pass-through mode of the stethoscope for demo.
2017-07-19 Commented the mixer level print statement to allow visualization of the rms and peaks from both acoustic inputs.
2017-07-19 Working version to trigger overalys on/off based on the microphone.
2017-07-19 Added logic that allows for rms amplitude peaks to play overlays only when the stethoscope is listening to periodic sounds.
2017-08-09 Added documentation on the stethoscope.
2017-08-11 Fragile/(VERY)buggy implementation of the uTrack paper method
2017-08-14 Convert virtual space into real space
2017-08-18 Improved IMU calibration (less variation)
2017-08-21 Created a script to test the solvers used in our process
2017-08-23 Partially fixed solvers
2017-08-28 VERSION: 0.1 First working version (still buggy)
2017-09-27 Fixed issue with newline characters not being printed
2017-10-02 Add files via upload
    Filled in some details of the first draft. Will continue to work on this.
    -Danny
2017-10-03 Computational approach rough draft
2017-10-04 Add files via upload
    Fundamental principles were elaborated on. Methods were fully explained. Results and Interpretation are all that remains, along with minor revisions and triple-checks for accuracy and grammatical con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
2017-10-06 Began developing a program that simulates the initial guesses of the magnetometers based on the shape of the triangulation
2017-10-09 Began adding corrections/suggestions to the current draft.
2017-10-10 K values for multiple magnets
2017-10-10 Pictures of IMU array & calibration process
2017-10-13 K value for spherical magnet
2017-10-13 minor tweaks
2017-10-17 Add files via upload
    Added the return for initial guess. Also changed the formatting. Hopefully, this looks nicer on the report.
2017-10-18 Include required libraries
2017-10-20 Add files via upload
    Both addresses are enabled to improve data sampling rates (s.t. half as many MUX switches are necessary).
    The right hand rule was enforced on sensor output to reflect a coordinate system definition that makes physical sense, and is consistent with the rest of the algorithm; the sensor's built-in C.S. was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
2017-10-26 Reverted to old setup
2017-10-30 Add files via upload
    Raw data and processing from which came the accuracy analysis
2017-10-31 Created a new document to include corrections made to the paper.
2017-10-31 Submitted the latest version of the magnetic tracking paper.
2017-11-06 Danny is the best
2017-11-07 Initial 3D plotting script
    Script is nasty, very slow, and buggy!
2017-11-08 Store data under UNIX systems
    Script is now capable of creating required directories and files to store data under a UNIX system
2017-11-10 Added a picture/figure of the current version of the audio patch diagram.
2017-11-10 Modified the blending function to enable RMS-based modulation
2017-11-12 Created new states as the blending function may need more complexity than it used to.
2017-11-13 Added the serial frame libraries to the main stethoscope arduino directory for ease in the compile process.
2017-11-13 Eliminated unused variables.
2017-11-13 Created different mixer steps for the different channels
2017-11-13 Completed a successful prototype of the rms-modulation of the signal. Need to explore floats for more precision and limits to avoid extreme attenuation or amplification.
2017-11-13 Began integrating a korotkoff blood pressure sound to the library of files
2017-11-13 Working triggering the same file on repeat, not successful yet...
2017-11-14 Formatting.
2017-11-14 Moving towards eliminating counters and using only timers.
2017-11-14 Stored time limits as variables. This was causing issues before, but it was associated with how elapsed millis was called.
2017-11-15 Added some recordings
2017-11-17 Basic code, albeit very messy, that serves as an example for 2 addresses
2017-11-20 Initial release of tracking code
2017-11-21 Began improving the start recording function within the stethoscope. By doing so, a need for several modes of recording became evident.
2017-12-01 Added serial monitor print statements to verify that string messages were sent correctly.
2017-12-01 Completed the development of a custom recording function, which takes an input string as the filename for the recording file.
2017-12-15 Meshing of STL files
2017-12-19 Remove unnecessary delay() calls
    Drastically improve data output rate from ~0.130s to ~0.030s
2018-01-04 Attach ILI934x library
2018-01-08 Display region magnet is within on TFT screen
2018-01-10 Draw current region instead of pulling image
2018-01-23 Store data into log file
2018-01-24 Correct K values
2018-01-26 DMD Paper V3 is in progress.
2018-01-29 Re-structure directories of the repository
2018-01-30 Updated the latest version of the paper and figures
2018-01-31 Updated the latest version, with Jacks comments.
2018-02-07 On the day of testing, for the new batch of stethoscopes, the microphone gain had to be dialed down to 24 for best results
2018-02-22 Workaround for TFT screen not working without monitor
2018-03-22 Final
2018-04-02 Re-organized the hardware directory and placed estimates and information pertaining to the latest PCB design
2018-04-17 Fix ACK spamming bug
2018-04-20 Deleted some out of place files
2018-04-20 Completed the integration of additional sounds for overlay
2018-05-02 Made formatting and labeling modifications to maintain consistency
2018-05-02 Began re-structuring the simulation functions
2018-05-02 This change will lead into the consolidation of file-specific blending functions to a more generic method
2018-05-07 Eliminated redundant calls for the compilation libraries
2018-05-07 Cleaned configuration header file
2018-05-08 Testes the sd card check function, which was previously unused
2018-05-08 Created a function called set-to-idle, which closes or terminates any function on the stethoscope and send the device to an idle state
2018-05-09 Created a new function for multichannels recoridng on the stethoscope. This will allow users to record the audio from the microphone and the speakers to proof/validate simulations are triggered corre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
2018-05-09 Integrated a file exists call to remove files with the same name previously stored in the SD card. Old files must be retrieved, so this should be very uncommon.
2018-05-09 Began working on a function that combines recording and blending for a somplete simulation
2018-05-10 Clean-up and renamed variables
2018-05-10 Added a low pass filter to the mic to speaker path/line to eliminate much of the ambient noise
2018-05-13 Successfully tested a cascading approach to the simulation process, by calling and reporting on several functions.
2018-05-13 Muted most print statements to verify the script its functioning as expected.
2018-05-13 Made modifications in an attempt to suppress the clicking sound but efforts seem useless. When eliminating the continue-recording function alltogether, the blending functions are muted. This may be o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
2018-05-13 Added the new files to the configuration file to be properly triggered by the stethoscope
2018-05-13 Created a set gains function to adjust gains related to the playback/overlay audio file. Also created a separate blending function to mitigate the effects of the switch mode function embedded within 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
2018-05-15 Moved the set gains function, also removed said function from the main loop. Finally integrated the set to idle function. Updated the SD cad on STET002.
2018-07-27 DRASTIC CHANGES! Re-defined initial structure with the filenames to be playback in order to simplify the number of function calls.
2018-07-27 Successfully created a function pair that looks for the right audio file and plays it without having to define many bytes and functions.
2018-07-27 Updated protocol definitions for stethoscopes
2018-07-31 Created a small routine to generate a byte array based on the length of available files
2018-07-31 Eliminated some comments used for troubleshooting and added some other messages to working functions.
2018-07-31 Successfully tested the sound blending with the new software.
2018-07-31 Moved the operational functions header file to the legacy folder instead of deleting it.
2018-08-01 Continued re-formatting the main program.
2018-08-01 Modified byte array order to avoid conflict
